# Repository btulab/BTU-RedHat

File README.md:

# BTU-RedHat

PCBs created for the 2017 Red Hat Summit

Licensed CC-BY BTU Lab

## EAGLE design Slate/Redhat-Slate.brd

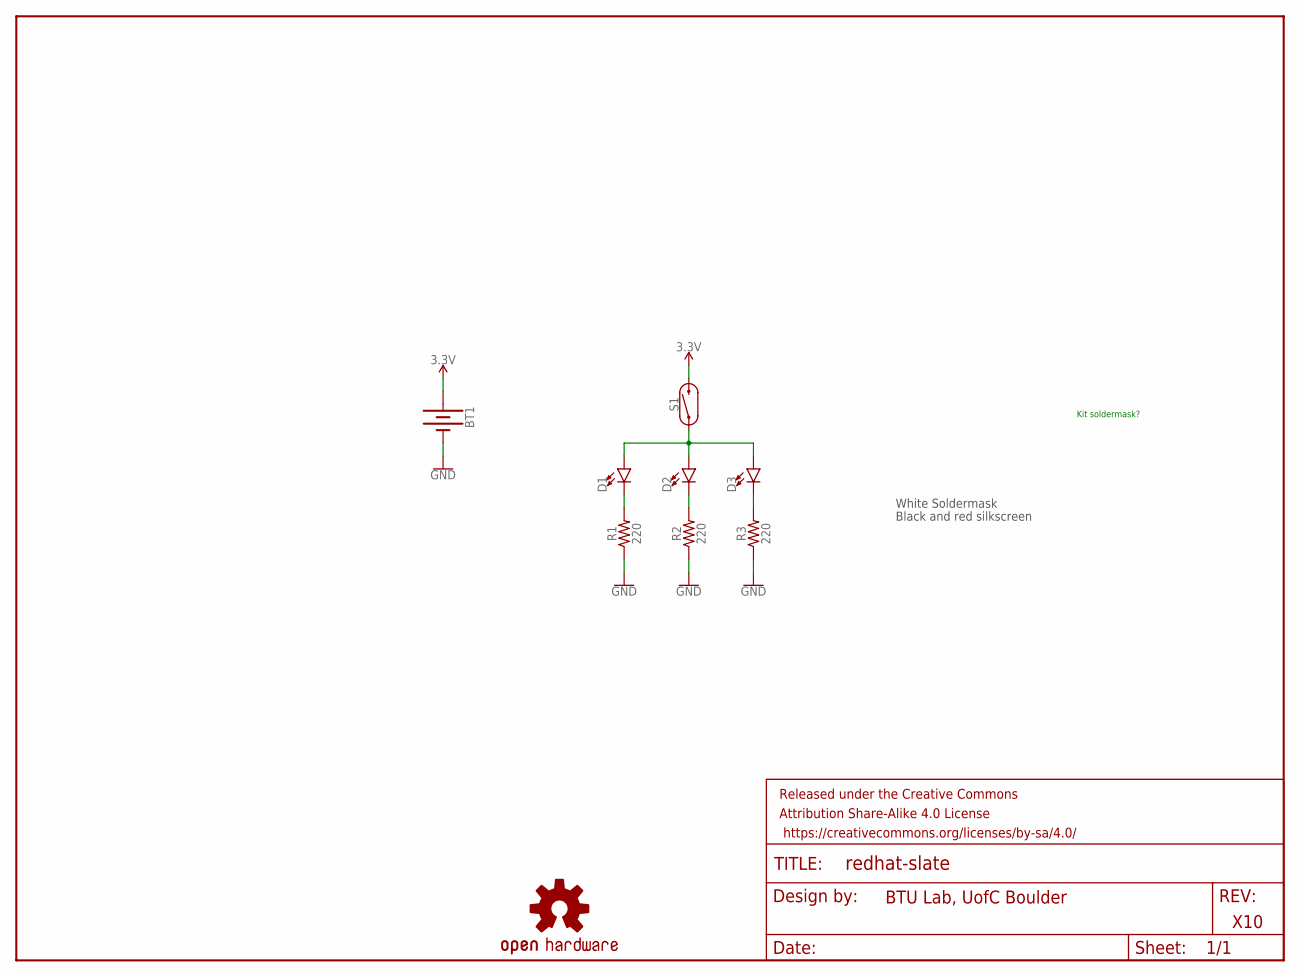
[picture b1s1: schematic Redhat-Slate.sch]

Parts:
BT1: BATTERY-20MM_PTH; BATTCOM_20MM_PTH
D1, D2, D3: LEDRED; LED_5MM_EXTRASILK
FRAME1: FRAME-LETTER; CREATIVE_COMMONS
LOGO4: OSHW-LOGOS; OSHW-LOGO-S
R1, R2, R3: 220; AXIAL-0.3
S1: REED_SWITCH-PTH-INSULATED; REED_SWITCH_PLASTIC

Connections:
3.3V: BT1.1 (+), S1.P$2 (2)
GND: BT1.2 (-), R1.P$1 (1), R2.P$1 (1), R3.P$1 (1)
unnamed: D1.K (C), R1.P$2 (2)
unnamed: D1.A, D2.A, D3.A, S1.P$1 (1)
unnamed: D2.K (C), R2.P$2 (2)
unnamed: D3.K (C), R3.P$2 (2)

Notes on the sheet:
X10
BTU Lab, UofC Boulder
Kit soldermask?
White Soldermask
Black and red silkscreen

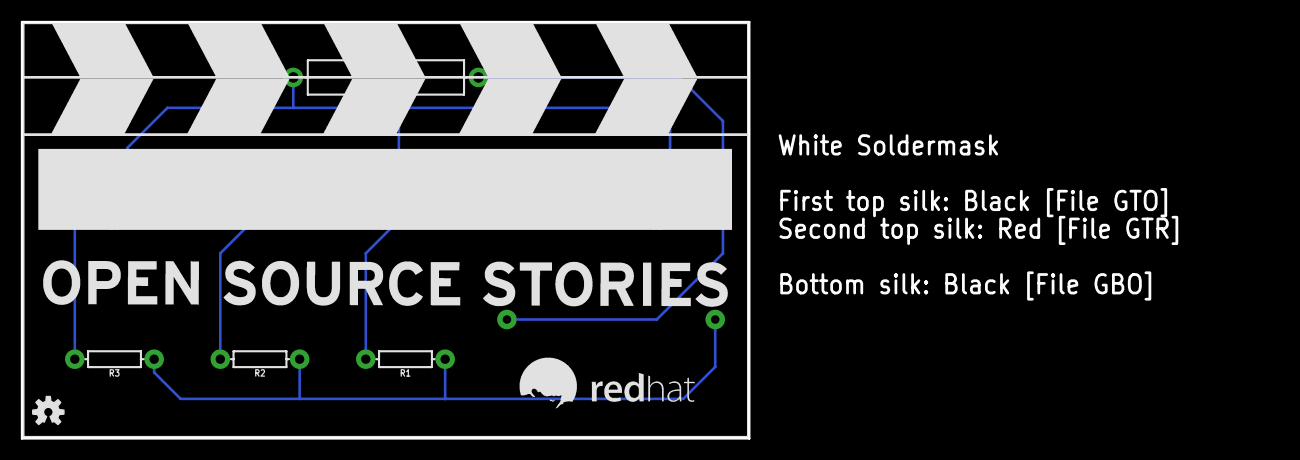
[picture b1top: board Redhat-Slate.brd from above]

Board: 2 copper layers, 120.6 x 40.0 mm, 10 parts (1 on the bottom side), 6 nets.

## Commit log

2017-05-02 Created README.md

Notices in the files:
parts and their libraries:
SparkFun-Aesthetics: Licensing: Creative Commons ShareAlike 4.0 International - https://creativecommons.org/licenses/by-sa/4.0
SparkFun-Aesthetics: Released under the Creative Commons Attribution Share-Alike 4.0 License
SparkFun-Aesthetics: https://creativecommons.org/licenses/by-sa/4.0
